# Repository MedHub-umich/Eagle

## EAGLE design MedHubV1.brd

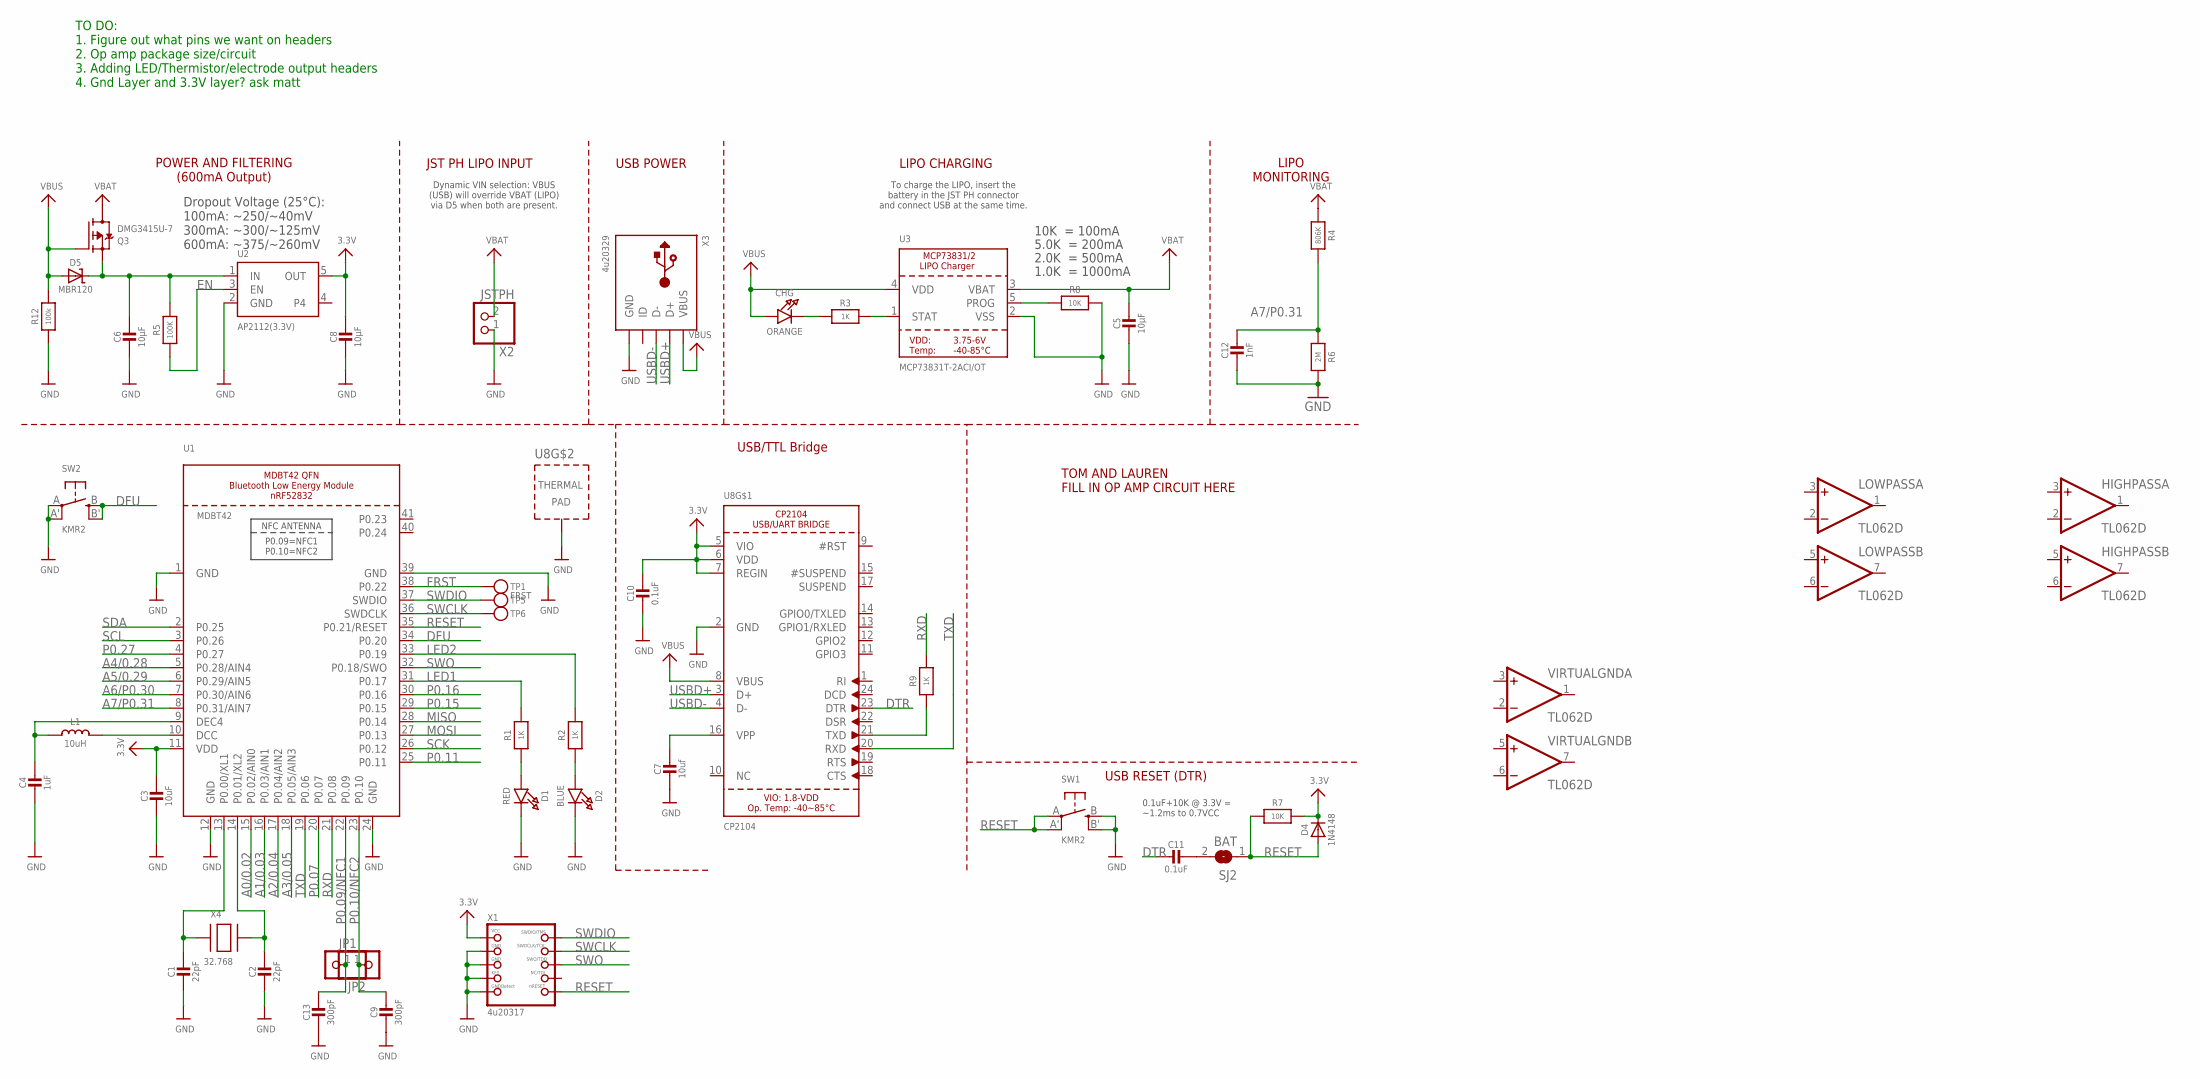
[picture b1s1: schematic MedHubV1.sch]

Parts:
C1, C2: 22pF; 0603-NO
C3: 10uF; 0805-NO
C4: 1uF; 0603-NO
C5, C6, C8: 10µF; 0805-NO
C7: 10uf; 0805-NO
C9, C13: 300pF; _0603MP
C10, C11: 0.1uF; 0603-NO
C12: 1nF; 0603-NO
CHG: ORANGE; CHIPLED_0805_NOOUTLINE
D1: RED; CHIPLED_0805_NOOUTLINE
D2: BLUE; CHIPLED_0805_NOOUTLINE
D4: 1N4148; SOD-323
D5: MBR120; SOD-123
HIGHPASS: TL062D; SO08
JP1, JP2: HEADER-1X12MM; 1X01_2MM
L1: 10uH; 0805-NO
LOWPASS: TL062D; SO08
Q3: DMG3415U-7; SOT23-R
R1, R2, R3, R9: 1K; 0603-NO
R4: 806K; 0603-NO
R5: 100K; 0603-NO
R6: 2M; 0603-NO
R7, R8: 10K; 0603-NO
R12: 100k; 0603-NO
SJ2: BAT; SOLDERJUMPER_CLOSEDWIRE
SW1, SW2: KMR2; BTN_KMR2_4.6X2.8
TP1: FRST; PAD-1.5X2.0
TP5, TP6: TESTPOINTROUND2MM; TESTPOINT_ROUND_2MM
U1: MDBT42; BLE_MODULE_RAYTAC_MDBT42
U2: AP2112(3.3V); SOT23-5
U3: MCP73831T-2ACI/OT; SOT23-5
U8: CP2104; QFN24_4MM_SMSC
VIRTUALGND: TL062D; SO08
X1: 4u20317; 2X05_1.27MM_BOX_POSTS
X2: JSTPH; JSTPH2
X3: 4u20329; 4UCONN_20329_V2
X4: 32.768; XTAL3215

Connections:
3.3V: C3.1, C8.1, C10.1, D4.C, R7.2, U1.11 (VDD), U2.5 (OUT), U8.5 (VIO), U8.6 (VDD), U8.7 (REGIN), X1.1 (VCC)
A0/0.02: U1.15 (P0.02/AIN0)
A1/0.03: U1.16 (P0.03/AIN1)
A2/0.04: U1.17 (P0.04/AIN2)
A3/0.05: U1.18 (P0.05/AIN3)
A4/0.28: U1.5 (P0.28/AIN4)
A5/0.29: U1.6 (P0.29/AIN5)
A6/P0.30: U1.7 (P0.30/AIN6)
A7/P0.31: C12.1, R4.2, R6.1, U1.8 (P0.31/AIN7)
DFU: SW2.B (S), SW2.B' (S1), U1.34 (P0.20)
DTR: C11.2, U8.23 (DTR)
EN: R5.1, U2.3 (EN)
FRST: TP1.P$1, U1.38 (P0.22)
GND: C1.2, C2.2, C3.2, C4.2, C5.2, C6.2, C7.2, C8.2, C9.2, C10.2, C12.2, C13.2, D1.C, D2.C, R6.2, R8.2, R12.1, SW1.B (S), SW1.B' (S1), SW2.A, SW2.A' (P1), U1.1 (GND), U1.12 (GND), U1.24 (GND), U1.39 (GND), U2.2 (GND), U3.2 (VSS), U8.2 (GND), U8.THERM (TP), X1.3 (GND), X1.5 (GND), X1.7 (KEY), X1.9 (GNDDETECT), X2.1, X3.BASE@1 (GND), X3.BASE@2 (GND), X3.GND, X3.SPRT@1 (GND), X3.SPRT@2 (GND), X3.SPRT@3 (GND), X3.SPRT@4 (GND)
LED1: R1.2, U1.31 (P0.17)
LED2: R2.2, U1.33 (P0.19)
MISO: U1.28 (P0.14)
MOSI: U1.27 (P0.13)
unnamed: C1.1, U1.13 (P0.00/XL1), X4.P$1
unnamed: C2.1, U1.14 (P0.01/XL2), X4.P$2
unnamed: D1.A, R1.1
unnamed: D2.A, R2.1
unnamed: L1.2, U1.10 (DCC)
unnamed: C4.1, L1.1, U1.9 (DEC4)
unnamed: CHG.C, R3.1
unnamed: R3.2, U3.1 (STAT)
unnamed: R8.1, U3.5 (PROG)
unnamed: R9.1, U8.21 (TXD)
unnamed: C11.1, SJ2.2
unnamed: C7.1, U8.16 (VPP)
P0.07: U1.20 (P0.07)
P0.09/NFC1: C13.1, JP2.1, U1.22 (P0.09)
P0.10/NFC2: C9.1, JP1.1, U1.23 (P0.10)
P0.11: U1.25 (P0.11)
P0.15: U1.29 (P0.15)
P0.16: U1.30 (P0.16)
P0.27: U1.4 (P0.27)
RESET: D4.A, R7.1, SJ2.1, SW1.A, SW1.A' (P1), U1.35 (P0.21/RESET), X1.10 (NRESET)
RXD: R9.2, U1.21 (P0.08)
SCK: U1.26 (P0.12)
SCL: U1.3 (P0.26)
SDA: U1.2 (P0.25)
SWCLK: TP6.P$1, U1.36 (SWDCLK), X1.4 (SWDCLK)
SWDIO: TP5.P$1, U1.37 (SWDIO), X1.2 (SWDIO)
SWO: U1.32 (P0.18/SWO), X1.6 (SWO)
TXD: U1.19 (P0.06), U8.20 (RXD)
USBD+: U8.3 (D+), X3.D+
USBD-: U8.4 (D-), X3.D-
V+: HIGHPASS.8 (V+), LOWPASS.8 (V+), VIRTUALGND.8 (V+)
V-: HIGHPASS.4 (V-), LOWPASS.4 (V-), VIRTUALGND.4 (V-)
VBAT: C5.1, Q3.3 (D), R4.1, U3.3 (VBAT), X2.2
VBUS: CHG.A, D5.A, Q3.1 (G), R12.2, U3.4 (VDD), U8.8 (VBUS), X3.VBUS
VIN1: C6.1, D5.C, Q3.2 (S), R5.2, U2.1 (IN)

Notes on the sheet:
10K = 100mA
5.0K = 200mA
2.0K = 500mA
1.0K = 1000mA
LIPO CHARGING
LIPO MONITORING
To charge the LIPO, insert the battery in the JST PH connector and connect USB at the same time.
POWER AND FILTERING (600mA Output)
JST PH LIPO INPUT
Dynamic VIN selection: VBUS (USB) will override VBAT (LIPO) via D5 when both are present.
Dropout Voltage (25°C): 100mA: ~250/~40mV 300mA: ~300/~125mV 600mA: ~375/~260mV
USB POWER
USB/TTL Bridge
USB RESET (DTR)
0.1uF+10K @ 3.3V = ~1.2ms to 0.7VCC
TO DO: 1. Figure out what pins we want on headers 2. Op amp package size/circuit 3. Adding LED/Thermistor/electrode output headers 4. Gnd Layer and 3.3V layer? ask matt
TOM AND LAUREN FILL IN OP AMP CIRCUIT HERE

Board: 2 copper layers, 49 parts (0 on the bottom side), 36 nets, no tracks yet.

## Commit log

2017-10-29 initial commit, added a few op amps to Maggie's zip file

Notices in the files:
parts and their libraries:
microbuilder: This work is placed in the public domain, and may be freely used for commercial and non-commercial work with the following conditions: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
